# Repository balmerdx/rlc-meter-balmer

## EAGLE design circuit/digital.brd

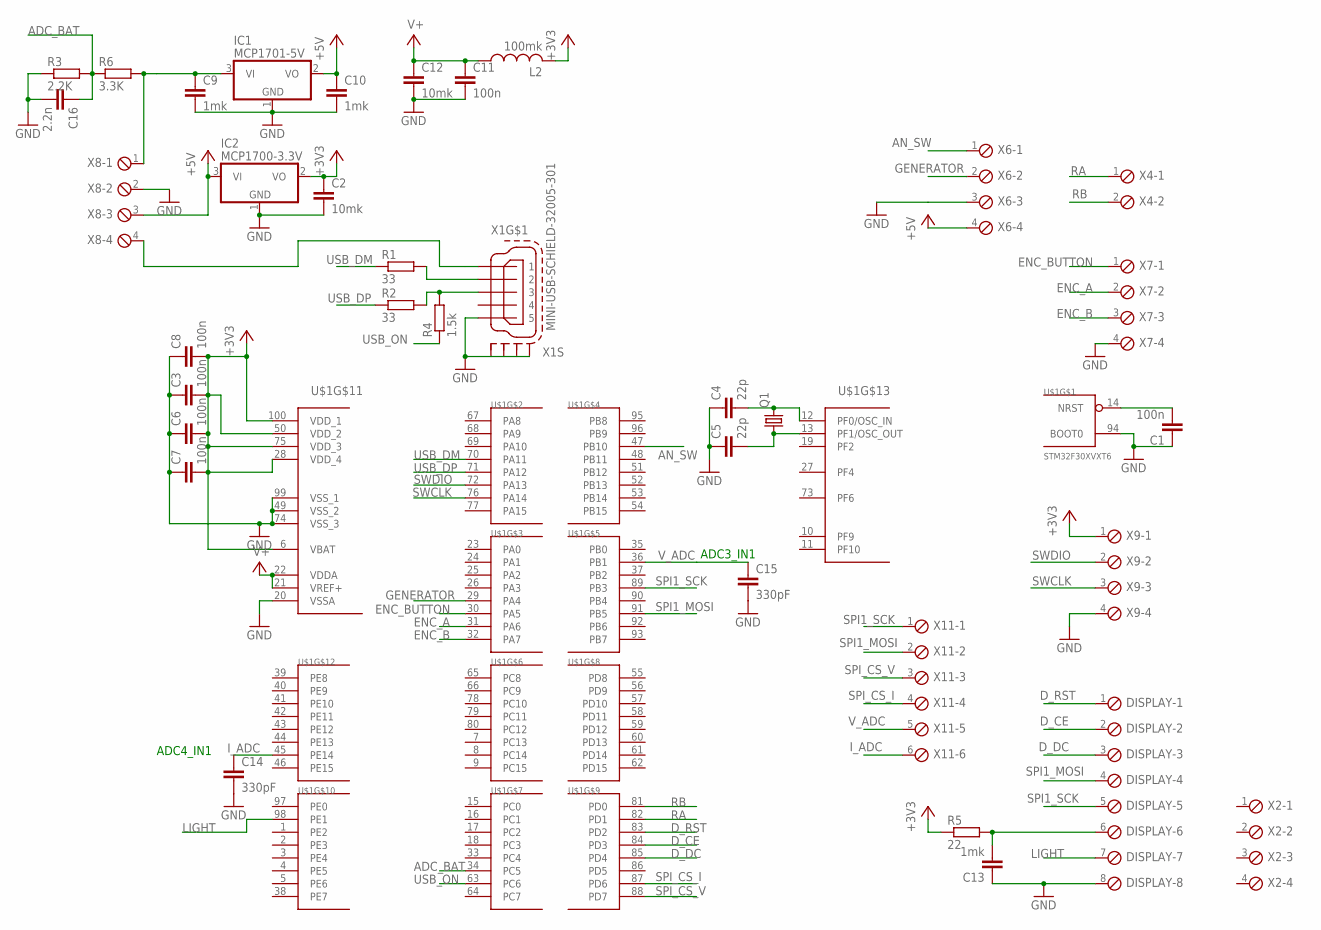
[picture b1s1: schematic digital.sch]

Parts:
C1, C3, C6, C7, C8, C11: 100n; C0603
C2, C12: 10mk; C0805
C4, C5: 22p; C0805
C9, C10, C13: 1mk; C0603
C14, C15: 330pF; C0805
C16: 2.2n; C0805
DISPLAY: MPT8; 8POL254
IC1: MCP1701-5V; SOT23
IC2: MCP1700-3.3V; SOT23
L2: 100mk; 0204/7
Q1: CRYSTALHC49UP; HC49UP
R1, R2: 33; R0603
R3: 2.2K; R0603
R4: 1.5k; R0603
R5: 22; R0603
R6: 3.3K; R0603
U$1: STM32F30XVXT6; TQFP100
X1: MINI-USB-SCHIELD-32005-301; 32005-301
X2, X6, X7, X8, X9: MPT4; 4POL254
X4: MPT2; 2POL254
X11: MPT6; 6POL254

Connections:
+3V3: C2.1, C3.2, C6.2, C7.2, C8.2, IC2.2 (VO), L2.2, R5.1, U$1.6 (VBAT), U$1.28 (VDD_4), U$1.50 (VDD_2), U$1.75 (VDD_3), U$1.100 (VDD_1), X9.1
+5V: C10.1, IC1.2 (VO), IC2.3 (VI), X6.4, X8.3
ADC_BAT: C16.1, R3.2, R6.1, U$1.34 (PC5)
AN_SW: U$1.47 (PB10), X6.1
D_CE: DISPLAY.2, U$1.84 (PD3)
D_DC: DISPLAY.3, U$1.85 (PD4)
D_RST: DISPLAY.1, U$1.83 (PD2)
ENC_A: U$1.31 (PA6), X7.2
ENC_B: U$1.32 (PA7), X7.3
ENC_BUTTON: U$1.30 (PA5), X7.1
GENERATOR: U$1.29 (PA4), X6.2
GND: C1.1, C2.2, C3.1, C4.1, C5.1, C6.1, C7.1, C8.1, C9.2, C10.2, C11.2, C12.2, C13.1, C14.2, C15.2, C16.2, DISPLAY.8, IC1.1 (GND), IC2.1 (GND), R3.1, U$1.20 (VSSA), U$1.49 (VSS_2), U$1.74 (VSS_3), U$1.94 (BOOT0), U$1.99 (VSS_1), X1.5, X1.M1 (S1), X1.M2 (S2), X1.M3 (S3), X1.M4 (S4), X6.3, X7.4, X8.2, X9.4
I_ADC: C14.1, U$1.45 (PE14), X11.6
LIGHT: DISPLAY.7, U$1.98 (PE1)
unnamed: R1.2, X1.2
unnamed: R2.2, R4.2, X1.3
unnamed: C1.2, U$1.14 (NRST)
unnamed: C4.2, Q1.2, U$1.12 (PF0/OSC_IN)
unnamed: C5.2, Q1.1, U$1.13 (PF1/OSC_OUT)
unnamed: C13.2, DISPLAY.6, R5.2
unnamed: C9.1, IC1.3 (VI), R6.2, X8.1
unnamed: X1.1, X8.4
RA: U$1.82 (PD1), X4.1
RB: U$1.81 (PD0), X4.2
SPI1_MOSI: DISPLAY.4, U$1.91 (PB5), X11.2
SPI1_SCK: DISPLAY.5, U$1.89 (PB3), X11.1
SPI_CS_I: U$1.87 (PD6), X11.4
SPI_CS_V: U$1.88 (PD7), X11.3
SWCLK: U$1.76 (PA14), X9.3
SWDIO: U$1.72 (PA13), X9.2
USB_DM: R1.1, U$1.70 (PA11)
USB_DP: R2.1, U$1.71 (PA12)
USB_ON: R4.1, U$1.63 (PC6)
V+: C11.1, C12.1, L2.1, U$1.21 (VREF+), U$1.22 (VDDA)
V_ADC: C15.1, U$1.36 (PB1), X11.5

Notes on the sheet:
ADC4_IN1
ADC3_IN1

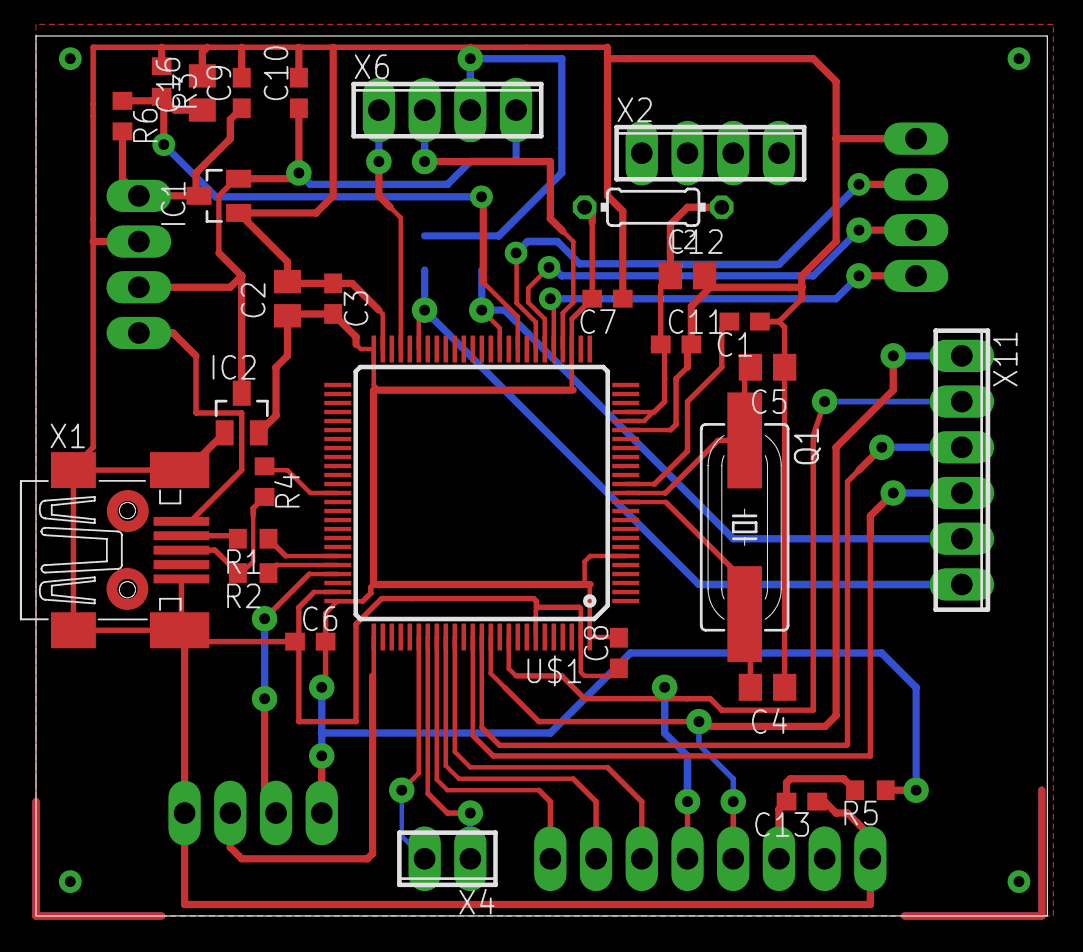
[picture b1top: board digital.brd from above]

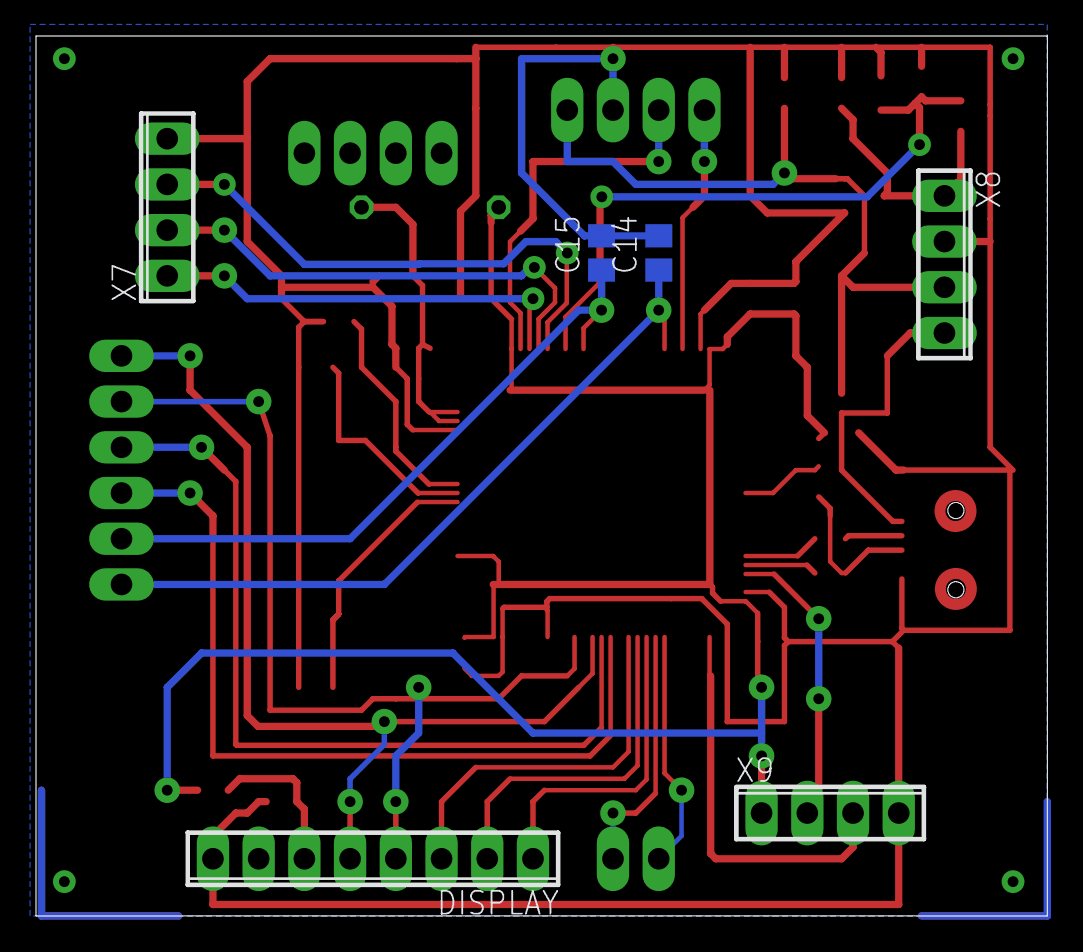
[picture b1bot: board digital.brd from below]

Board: 2 copper layers, 56.2 x 48.9 mm, 36 parts (6 on the bottom side), 35 nets.

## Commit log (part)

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2013-10-26 - первоначальный билд
2013-10-27 - analog to dual ADC STM32F103
2013-10-27 - будем полностью перерисовывать под другие усилители , AD8532 имеет слишком высокий Input offset voltage.
2013-10-27 - AD825, OP07C используем как усилители
2013-10-28 - начали разводить плату
2013-10-29 - черновой вариант разводки, не проверяли как земля разведенна. Не добавляли пинов, чтобы осциллографом цепляться
2013-10-29 - SO8
2013-10-29 - пины для теста
2013-10-31 - исходный код скопипастили для F103 демоплатки
2013-11-03 - DAC 100 khz STM32F107
2013-11-04 - настроили delay_us, delay_ms чтобы правильно время меряло
2013-11-05 - systick теперь считает верно, не конфликтует с USB, но максимум до 200 ms - работает USB на STM32F107 - устанавливается чатота
2013-11-07 - запускаем ADC по таймеру
2013-11-08 - читаем синусоидальный сигнал и пишем его в файл
2013-11-09 - запускаем синхронизированно ADC и DAC
2013-11-09 - немного математики для определения амплитуды и угла
2013-11-10 - корректно работает интервал 600 герц - 100 кгц
2013-11-10 - умеем считывать данные кучками
2013-11-11 - всякие ненужные изменения
2013-11-11 - dual mode
2013-11-17 - схема с установкой резисторов - начали разрабатывать третью версию аналоговой части
2013-11-17 - добавили делитель на генератор
2013-11-18 - убрали лишний конденсатор
2013-11-19 - первый вариант разводки под два LM258 в качестве опорного напряжения
2013-11-19 - забыли один Unrouted
2013-11-24 - начали делать цифровую часть
2013-11-24 - развели все пины идущие к аналоговой части
2013-11-24 - все кроме LCD дисплея
2013-11-24 - вывели 4 IO пина на всяк случай, для LCD
2013-11-24 - пару кружков под USB
2013-11-27 - 0.25 мм выводы у STM32
2013-12-10 - подтяжка по USB
2013-12-10 - начинаем разработку под STM32F303
2013-12-10 - usb работает на отправку тестового сообщения с девайса.
2013-12-10 - данные приходят и отсылаются. Правда бажину с тем, что первые данные не приходят на девайс - так и не побороли.
2013-12-11 - работающий DAC
2013-12-13 - неработающий ADC
2013-12-14 - в continuous режиме работает сдвоенное ADC
2013-12-14 - работающий на частоте 1.2 mhz adc с запуском от таймера
2013-12-15 - перенастроили DAC чтобы работал с чатотой 1 MHz
2013-12-15 - корректно работает в диапазоне 100 Гц - 100 КГц
2013-12-16 - косметические изменения
2013-12-16 - настроили ADC34
2013-12-19 - сломали Dual Mode, зато теперь работает Circular режим
2013-12-19 - теперь корректно работает DAC в Dual Mode с циклическим чтением.
2013-12-24 - разобрались с резисторами - график по кругу
2013-12-25 - переделали аналоговую часть под более быстрый усилитель - убрали неработающие микроиндуктивности, поставили индуктивность побольше - подставили дополнительный конденсатор на +2.5V
2013-12-30 - перед тем, как будем заводить SPI
2014-01-01 - управление коэффициэнтом усиления - запись данных в json формат
2014-01-02 - автоматический выбор коэффициентов усиления и запись их в json
2014-01-05 - высчитываем таки индуктивность и емкость
2014-01-05 - возможность усреднять данные
2014-01-06 - первый вариант подсчета на лету, который успевает, хотя и не все считает
2014-01-06 - немного ускорили подсчет
2014-01-06 - важный volatile для release режима - успеваем довольно быстро посчитать min, max, mid
2014-01-07 - версия, которая почти успевает считать sin, cos свертку
2014-01-08 - перешли на новый вариант сэмплирования данных, теперь не будет проблем с «не успеваем»
2014-01-08 - более-менее разумное вычисление sin/cos - какойто непонятный баг с повторным запуском расчетов в то время, когда они читаются
2014-01-08 - точность вычисления sin/cos на уровне точности float
2014-01-09 - нашли ошибку, из-за которой постоянно начинался новый обсчет.
2014-01-11 - сделали автоматический выбор резистора
2014-01-12 - переходим потихоньку на обработку данных на стороне микроконтроллера
2014-01-12 - возможность строить графики зависимости от частоты - потвикали автоматический выбор диапазона и амплитуду DAC сигнала, чтобы не заходило в нелинейную область
2014-01-12 - x10 усреднение для граяиков по частоте
2014-01-13 - вынесли вычисления в отдельный файл - вычисляем среднеквадратическую ошибку
2014-01-15 - первоначальные попытки калибровки
2014-01-15 C2 100 p -> 33 p R30 100 K -> 56 K - перенастроили соответственно уровни усиления
2014-01-20 - перед коррекцией по трем параметрам
2014-02-02 - перед заливкой 3 demo
2014-02-02 - 3demo для того чтобы отладить работу с дисплеем
2014-02-02 - система начинает работать
2014-02-02 - работает хардварный SPI2
2014-02-03 - читаем давление и температуру с датчика LPS331AP
2014-02-05 - стерли старые аналоговые схемы - стерли Hi Lo WaterMark
2014-02-05 - переделали SPI 8 bit на SPI 16 bit - уменьшили ненужное дерганье ножек - LcdStr, LcdChr принимают char строки
2014-02-08 - на цифровой схеме добавили разъем для Nokia 5110, коннекторы для переключения питания, объединили восточный разъем - на аналоговой схеме добавили включение 3.3 nF конденсатор, для фильтрации высоко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
2014-02-08 - перенесли конденсаторы фильтрующие частоту для ADC на цифровую часть схемы
2014-02-08 - совместили северные контакты - добавили RC цепочки между первым и вторым каскадом усиления - добавили неподключеный коннектор, чтобы было на чем держаться дисплею
2014-02-09 - цифровая схема, которую будем печатать
2014-02-11 - работающий quadrature encoder
2014-02-11 - прикрутили кнопку от энкодера
2014-02-12 - прикрутили коннектор для энкодера
2014-02-12 - переместили схемы чуть ниже, чтобы уместиться в 49 мм высоты
2014-02-12 - по краям насечки для винтов
2014-02-13 - слили вместе GND и GNDA - добавили измерение VBAT напряжения
2014-02-13 - Vbat таки подключать к питанию, а не к земле
2014-02-16 - завели софтварный SPI1
2014-02-16 - корректно работает HARDWARE SPI1
2014-02-17 - поменяли местами питание и землю
2014-02-23 - допаяли схему. - PC6 USB_ON подключили - PB10 AN_SW подключили
2014-02-25 - добавили поддержку дисплея
2014-03-08 - наметки по графическому интерфейсу
2014-03-10 - графики вызываемые черем main.py
2014-03-16 - попытка коррекции фазы - начали корректировку по сопротивлениям
2014-03-22 - ввели команду задания амплитуды сигнала для DAC
2014-03-22 - корректировка изменяющегося коэффициента усиления в зависимости от частоты.
2014-03-26 - посчитали коэффициэнты усиления в зависимости от частоты (только x32 не посчитали)
2014-03-28 - модальные диалоги - сделана часть, отвечающая за калибровку по сопротивлениям краев диапазона
2014-03-29 Кнопки для IV калибровки
2014-03-29 - диалог open/short калибровки
2014-03-29 - прикрутили автоматический выбор диапазона
2014-03-31 - мелкие изменения
2014-04-02 - автоматический выбор корректировки
2014-04-03 - облагородили меню графиков
2014-04-05 - меню для измерения при определенной частоте
2014-04-05 - более удобное представление LC - serial/parallel для R
2014-04-06 - учитываем, что из-за ошибок калибрации может быть немного отрицательная емкость и индуктивность
2014-04-10 - ужали схему по размерам, чтобы на один лист влезала
2014-04-11 - небольшой рефактор GainCorrector
2014-04-13 - calculateJson возвращает сразу комплексное сопротивление
2014-04-13 - избавились от промежуточных тригонометрических операций при вычислении комплексного сопротивления
2014-04-17 - автоматически выбираем резистор на контроллере
2014-04-18 - автоматический выбор коэффициэнта усиления на микроконтроллере
2014-04-19 - predefinedResistorIdx для startGainAuto
2014-04-20 - выбираем хардварно данные с суммированием
2014-04-20 - вычисление сопротивления на девайсе
2014-04-20 - вывод сопротивления в человеческом виде
2014-04-22 - корректировка по коэффициенту усиления
2014-04-25 - работающий Corrector2x в железе
2014-04-25 - open корректировка
2014-04-26 - struct CoeffCorrector
2014-04-26 - запись корректирующих коэффициэнтов во flash
2014-04-26 - automatic set low pass
2014-04-27 - визуализация частоты
2014-04-28 - большие цифирки
2014-04-28 - кажется dev.reset() помогает читать данные с usb девайса начиная с первого байта!
2014-05-01 - отображение LC - SER/PAR схема замещения
2014-05-01 - в continuous mode если не сильно изменилось значение, не пересчитываем заново результат
2014-05-09 - quadrature encoder code
2014-05-10 - TIM7 50 ms interrupt to button up/down check
2014-05-11 - menu frequency ser/par
2014-05-11 - запоминаем поседний выделенный пункт меню - выбираем для визуализации Rim или L/C
2014-05-11 - таки разобрались, из-за чего на сопротивлениях 200-300 ом было большое Rim это было из-за слишком большой амплитуды колебаний!
2014-05-19 - PE1 - light control pin
2014-05-20 - корректно работает при отключенном USB
2014-05-20 - считываем напряжение с батарейки
2014-05-20 - рисуем батарейку
2014-05-21 - отображение "свежести" батареи
2014-05-24 - сделали щупы - актуализировали диалог калибровки
2014-05-28 - новый вариант GainCorrector, ничуть не лучше старого
2014-06-01 - новый вариант калибровки, без использования gain_corrector
2014-06-01 - обновили значения элементов
2014-06-01 - разобрались с многопоточной отсылкой сообщений - начали работу над OPEN калибровкой
2014-06-04 - корректировка диапазона больше 100 КОм. - правильно калибруем open щупы чтобы при большом усилении и частоте перегрузки не было
2014-06-06 - перед переделкой корректирующих коэффициэнтов в железке
2014-06-06 - начали переделку corrector.c - корректно выбираем коэффициэнты усиления на центральных диапазонах - делаем правильную коррекцию при помощи corrector2x
2014-06-07 - исправили ошибку определения gain индексов (ошибалось на 1 диапазон)
2014-06-07 - корректная open корректировка в железе
2014-06-07 - запись во flash - еще уменьшили диапазон для ADC, получили неплохой буст к точности
2014-06-08 - корректировка 1 Ом - ограничение усиления на высоких частотах в железе - 250 КГц частота в железе
2014-06-09 - стер устаревшую директорию code - поменял сообщение о владельце проекта
2014-06-09 переименовали voltage.c -> usb_commands.c
2014-06-09 - add pdf circuit
2014-06-10 - infos
2014-06-10 - update source.mk
2014-06-14 - больше не используем load-load калибровку, заменили ее на open-load, так меньше фазовый шум.
2014-06-14 - 187.5 КГц частота
2014-06-14 - улучшили заставку - вывели угол printGradus = carg(Zx)...
2014-07-03 - dсякие мелкоскопические изменения
2014-07-03 - откомпилированная версия прошивки
2014-07-07 - вариант прошивки где используется 3 кнопки для управления вместо энкодера
2014-07-08 - поменял местами кнопки A и B
2014-07-25 - убрали ненужные USB descriptions
2014-07-25 - длинное меню, выходящее за пределы экрана
2014-07-25 - простецкий редактор цифр для калибровки
2014-07-26 - MessageBox
2014-07-26 - ClearCorrector - если корректирующие коэффициэнты не найдены, то частота отображается инверсно
2014-07-29 - код для калибрации (нерабочий пока еще) - можем запускать калибрацию, на экране это видно - корректно ждем, когда пройдут переходные процессы.
2014-07-30 - onboard short correction
2014-07-30 - калибровки дипазоне от 0 до 100 КОм - обновили прошивки
2014-07-31 - open calibration
2014-08-01 - очищаем flash перед записью корректирующих коэффициэнтов - пункт меню CLEAR - очищает корректировку только для текущей частоты
2014-08-01 - исправил медленное обновление экрана при измерении высоких частот
2014-08-15 - работа с ili9341 дисплеем - перенесли пример работы с pcd8544 дисплеем в отдельную папку
2014-09-24 - AD9958 first code
2014-11-19 - при инициализации STD периферии надо инициализировать все поля, иначе могут быть "неожиданные ошибки"
2014-11-26 - AD9959 CH3 работает
2015-12-12 - пробуем помочь rav133
2015-12-12 - сборка для rav133
2015-12-12 - выключил у DAC буфер - откатил изменения - еще одна прошивка
2015-12-14 - еще раз обновил прошивку.
2016-05-06 Нарисовал таки PE1 - управление backlight
2016-05-07 Обновил прошивки Errors% и SetR дебаговые пункты меню.
2016-05-21 - qt4 - libusb 1.0
2016-05-21 Корретная колибровка. Корректный вывод графиков.
2016-05-31 Возможно, под другими OS не вызывалось OnSliderReleased и из-за этого не работало.
